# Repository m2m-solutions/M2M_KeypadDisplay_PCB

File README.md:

# M2M_KeypadDisplay_PCB
Eagle PCB project for the M2M keypad display

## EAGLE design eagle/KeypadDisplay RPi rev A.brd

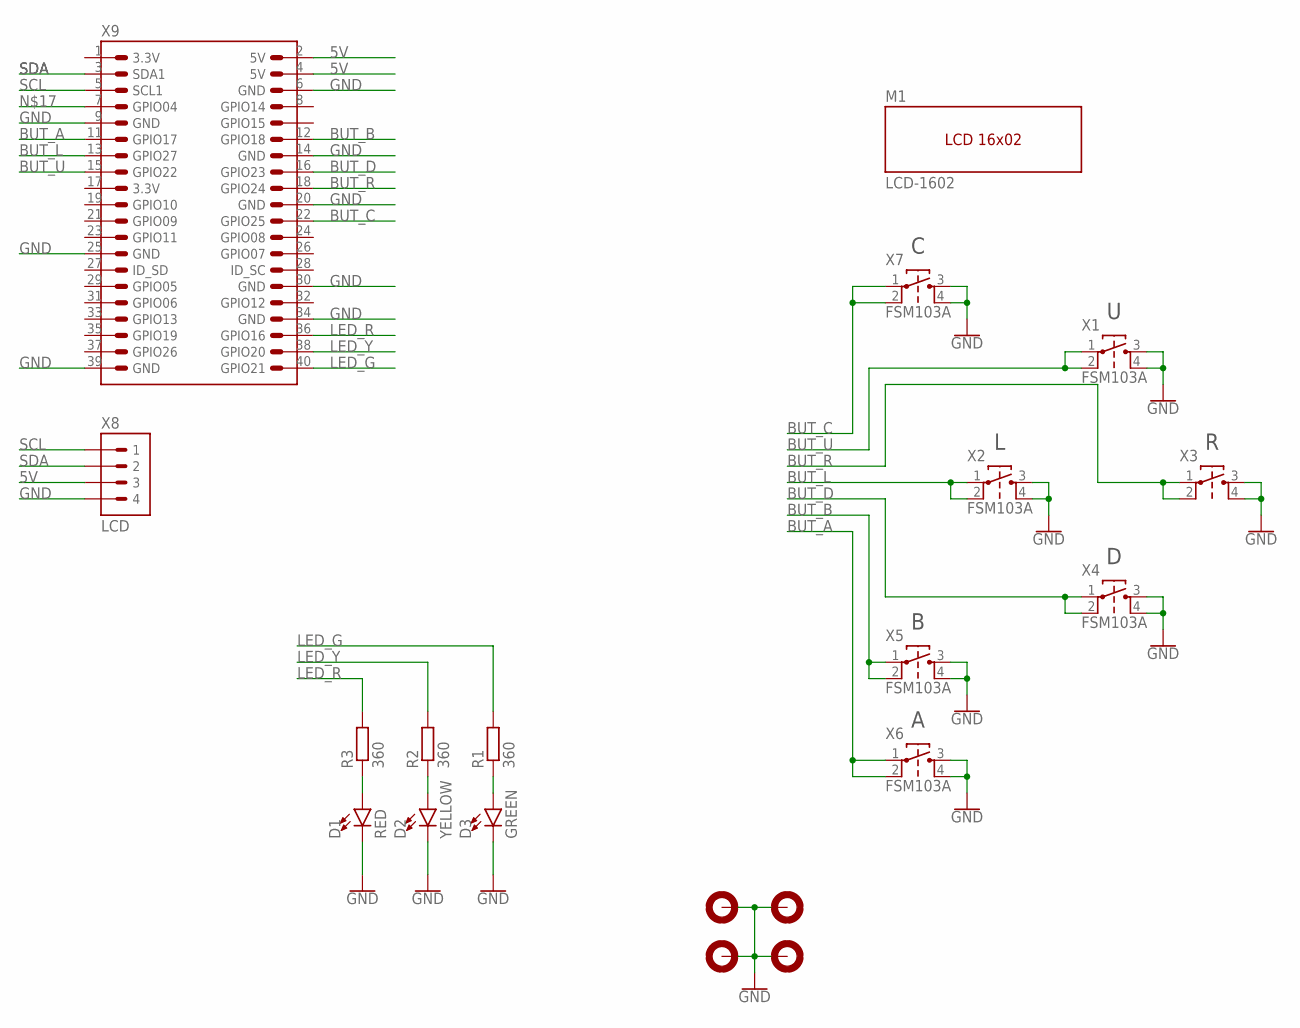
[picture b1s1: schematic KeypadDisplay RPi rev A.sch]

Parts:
D1: RED; LED5MM
D2: YELLOW; LED5MM
D3: GREEN; LED5MM
H1, H2, H3, H4: MOUNTHOLE-PAD3.0; 3.0-PAD
M1: LCD-1602; LCD-1602-NOHEADER
R1, R2, R3: 360; 0204/7
X1, X2, X4, X5, X6, X7: FSM103A; TACT-SWITCH-FSM103A
X3: TACT-SWITCHFSM103A; TACT-SWITCH-FSM103A
X8: LCD; 1X04P-2.54
X9: HEADER-RPI-2X20; 2X20-2.54

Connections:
3.3V: X9.1 (3.3V), X9.17 (3.3V)
5V: X8.3, X9.2 (5V), X9.4 (5V)
BUT_A: X6.1 (A), X6.2 (A'), X9.11 (GPIO17)
BUT_B: X5.1 (A), X5.2 (A'), X9.12 (GPIO18)
BUT_C: X7.1 (A), X7.2 (A'), X9.22 (GPIO25)
BUT_D: X4.1 (A), X4.2 (A'), X9.16 (GPIO23)
BUT_L: X2.1 (A), X2.2 (A'), X9.13 (GPIO27)
BUT_R: X3.1 (A), X3.2 (A'), X9.18 (GPIO24)
BUT_U: X1.1 (A), X1.2 (A'), X9.15 (GPIO22)
GND: D1.K (C), D2.K (C), D3.K (C), H1.B3,2, H2.B3,2, H3.B3,2, H4.B3,2, X1.3 (B), X1.4 (B'), X2.3 (B), X2.4 (B'), X3.3 (B), X3.4 (B'), X4.3 (B), X4.4 (B'), X5.3 (B), X5.4 (B'), X6.3 (B), X6.4 (B'), X7.3 (B), X7.4 (B'), X8.4, X9.6 (GND), X9.9 (GND), X9.14 (GND), X9.20 (GND), X9.25 (GND), X9.30 (GND), X9.34 (GND), X9.39 (GND)
LED_G: R1.2, X9.40 (GPIO21)
LED_R: R3.2, X9.36 (GPIO16)
LED_Y: R2.2, X9.38 (GPIO20)
unnamed: D1.A, R3.1
unnamed: D2.A, R2.1
unnamed: D3.A, R1.1
SCL: X8.1, X9.5 (SCL1)
SDA: X8.2, X9.3 (SDA1)

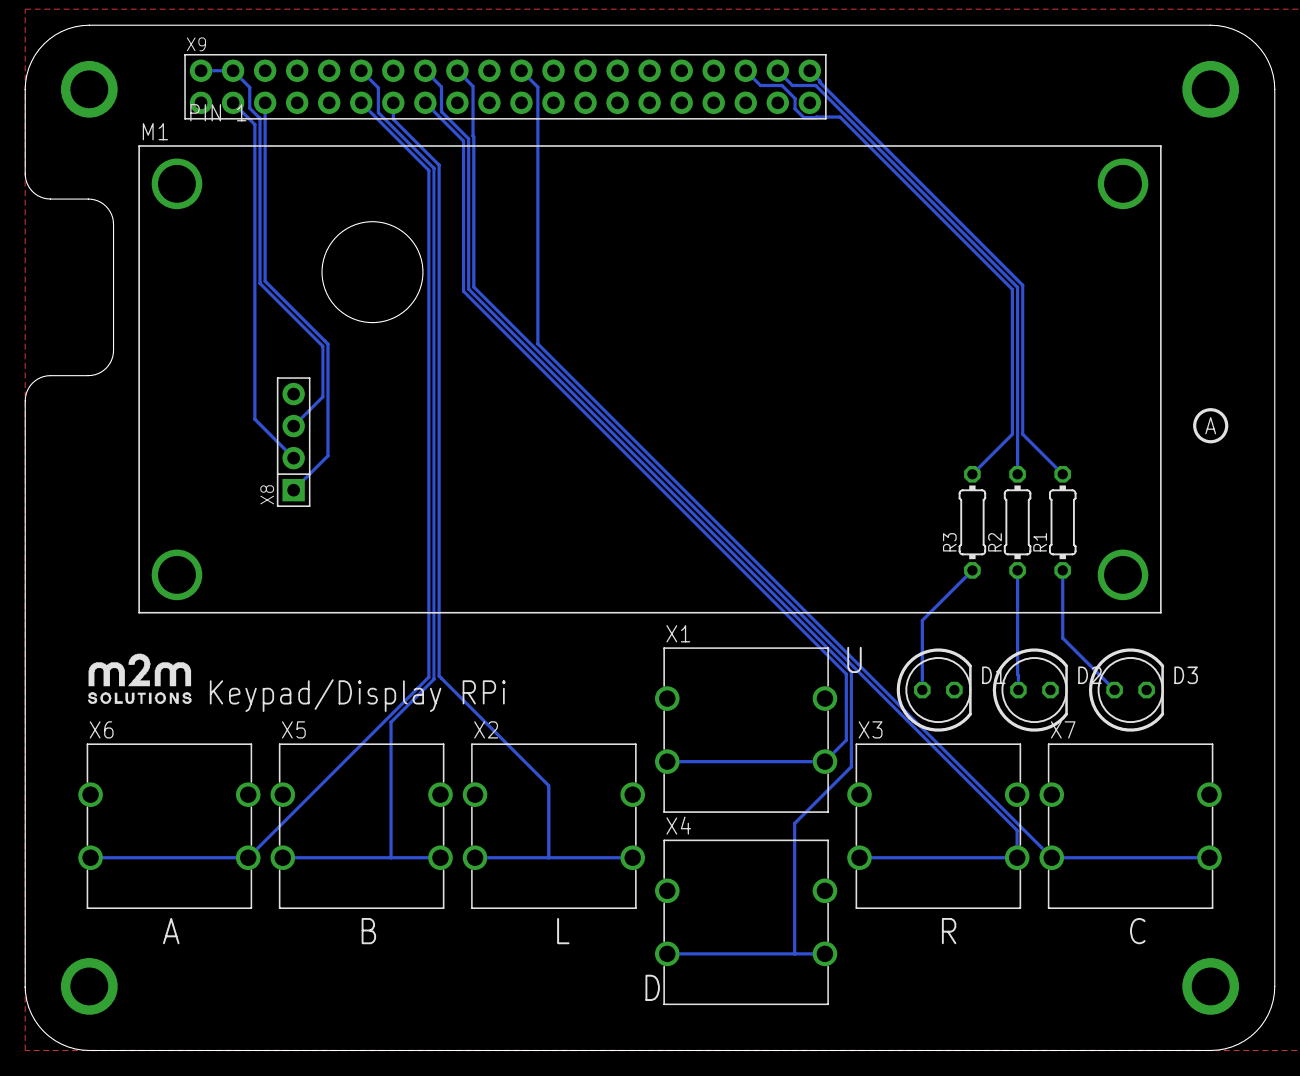
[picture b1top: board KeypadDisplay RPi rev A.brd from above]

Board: 2 copper layers, 99.1 x 81.3 mm, 22 parts (0 on the bottom side), 18 nets.

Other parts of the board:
U$1: M2M-10MMB
U$2: M2M-LOGO-4MM

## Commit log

2019-07-30 Initial checkin
2019-08-17 Added PCB for Raspberry Pi
